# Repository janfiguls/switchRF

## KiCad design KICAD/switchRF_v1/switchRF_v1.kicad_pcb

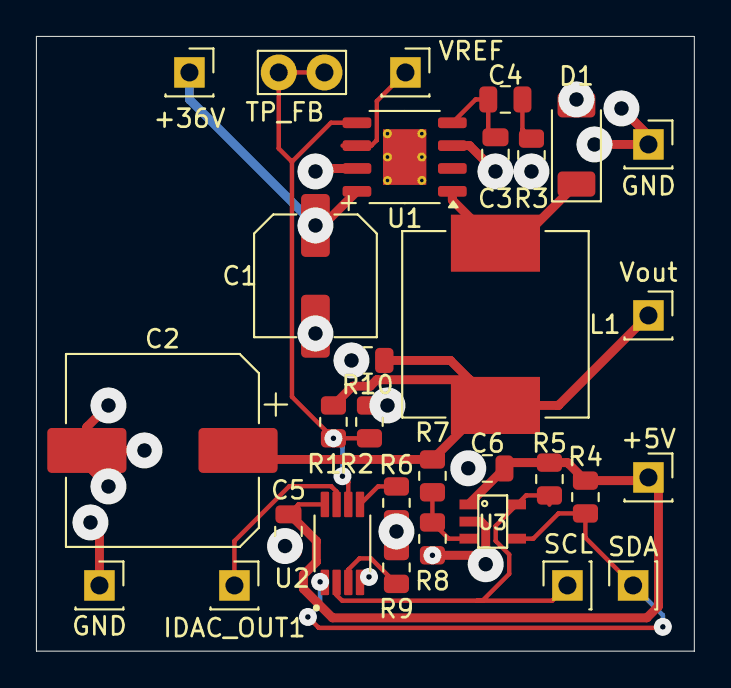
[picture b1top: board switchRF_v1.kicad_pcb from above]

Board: 2 copper layers, 36.6 x 34.2 mm, 31 parts (0 on the bottom side), 15 nets.

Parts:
+5V: +5V; PinSocket_1x01_P2.54mm_Vertical
+36V: +36V; PinSocket_1x01_P2.54mm_Vertical
C1: 10u; CP_Elec_6.3x5.3
C2: 220u; CP_Elec_10x14.3
C3: 220p; C_0805_2012Metric
C4: 22n; C_0805_2012Metric
C5, C6: 100n; C_0805_2012Metric
D1: 60V,3A; D_SOD-128
GND: GND; PinSocket_1x01_P2.54mm_Vertical
GND#2: GND; PinSocket_1x01_P2.54mm_Vertical
IDAC_OUT1: IDAC_OUT1; PinSocket_1x01_P2.54mm_Vertical
L1: 15u; L_Vishay_IHLP-4040
R1: 300k; R_0805_2012Metric
R2: 100k; R_0805_2012Metric
R3, R4, R5: 4.7k; R_0805_2012Metric
R6, R9: 80k; R_0805_2012Metric
R7: 200k; R_0805_2012Metric
R8: 20k; R_0805_2012Metric
R10: 50k; R_0805_2012Metric
SCL: SCL; PinSocket_1x01_P2.54mm_Vertical
SDA: SDA; PinSocket_1x01_P2.54mm_Vertical
TP_FB: Test_FB; TestPoint_Bridge_Pitch2.54mm_Drill1.0mm
U1: L5973D; HSOP-8-1EP_3.9x4.9mm_P1.27mm_EP2.41x3.1mm_ThermalVias
U2: DS4432U_; SOP65P490X110-8N
U3: MCP3021; SOT-23
VREF: VREF; PinSocket_1x01_P2.54mm_Vertical
Vout: Vout; PinSocket_1x01_P2.54mm_Vertical

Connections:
+5V: +5V.1, C5.1, C6.1, R4.2, R5.2, U2.8 (VCC), U3.P$1 (VCC)
+36V: +36V.1, C1.1, U1.8 (VCC)
/SCL: R5.1, SCL.1, U2.2 (SCL), U3.P$5 (SCL)
/SDA: R4.1, SDA.1, U2.1 (SDA), U3.P$4 (SDA)
/Vbuck_out: D1.1 (K), L1.1, U1.1 (OUT)
/Vout: C2.1, L1.2, R1.1, R7.1, R10.1, Vout.1
GND: C1.2, C2.2, C3.2, C5.2, C6.2, D1.2 (A), GND.1, GND#2.1, R2.2, R3.2, R6.1, R8.2, R9.1, R10.2, U1.3 (INH), U1.7 (GND), U2.4 (GND), U3.P$2 (GND)
unnamed: C4.2, R3.1
unnamed: U1.6 (VREF), VREF.1
unnamed: IDAC_OUT1.1, U2.7 (OUT1)
unnamed: C3.1, C4.1, U1.4 (COMP)
unnamed: R1.2, R2.1, TP_FB.1, U1.5 (FB), U2.6 (OUT0)
unnamed: R6.2, U2.5 (FS0)
unnamed: R9.2, U2.3 (FS1)
unnamed: R7.2, R8.1, U3.P$3 (AIN)

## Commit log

2025-01-28 Created dummy README.txt
